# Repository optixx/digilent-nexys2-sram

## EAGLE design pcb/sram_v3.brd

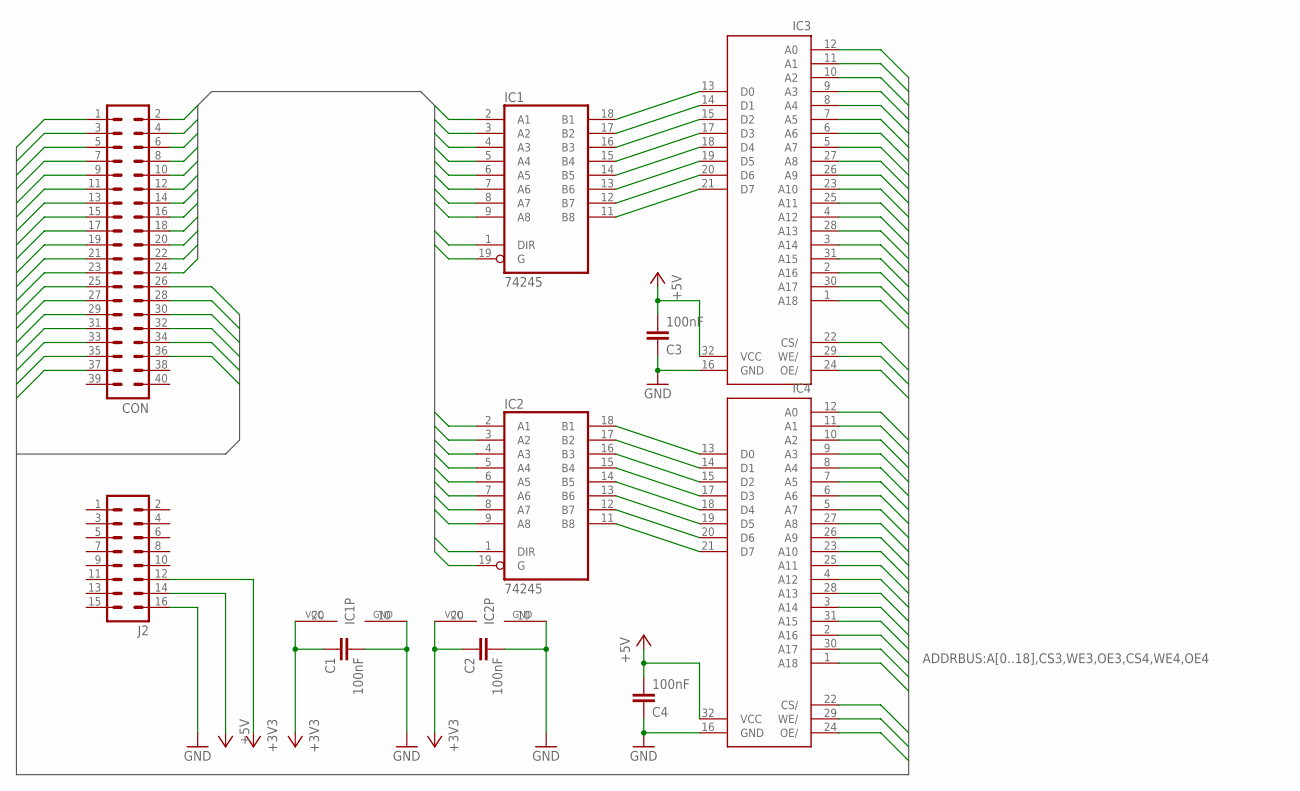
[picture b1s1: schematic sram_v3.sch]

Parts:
C1, C2, C3, C4: 100nF; C050-030X075
CON: ML40
IC1, IC2: 74245; TSSOP20
IC3, IC4: MEMORY-SAMSUNG-2_KM628512-XX; MEMORY-SAMSUNG-2_SOP-32
J2: ML16

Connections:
+3V3: C1.1, C2.1, IC1.20 (VCC), IC2.20 (VCC), J2.12
+5V: C3.2, C4.2, IC3.32 (VCC), IC4.32 (VCC), J2.14
A0: CON.37, IC3.12 (A0), IC4.12 (A0)
A1: CON.35, IC3.11 (A1), IC4.11 (A1)
A2: CON.33, IC3.10 (A2), IC4.10 (A2)
A3: CON.31, IC3.9 (A3), IC4.9 (A3)
A4: CON.29, IC3.8 (A4), IC4.8 (A4)
A5: CON.27, IC3.7 (A5), IC4.7 (A5)
A6: CON.25, IC3.6 (A6), IC4.6 (A6)
A7: CON.23, IC3.5 (A7), IC4.5 (A7)
A8: CON.21, IC3.27 (A8), IC4.27 (A8)
A9: CON.19, IC3.26 (A9), IC4.26 (A9)
A10: CON.17, IC3.23 (A10), IC4.23 (A10)
A11: CON.15, IC3.25 (A11), IC4.25 (A11)
A12: CON.13, IC3.4 (A12), IC4.4 (A12)
A13: CON.11, IC3.28 (A13), IC4.28 (A13)
A14: CON.9, IC3.3 (A14), IC4.3 (A14)
A15: CON.7, IC3.31 (A15), IC4.31 (A15)
A16: CON.5, IC3.2 (A16), IC4.2 (A16)
A17: CON.3, IC3.30 (A17), IC4.30 (A17)
A18: CON.1, IC3.1 (A18), IC4.1 (A18)
CS3: CON.26, IC3.22 (CS/)
CS4: CON.32, IC4.22 (CS/)
D0: CON.16, IC1.2 (A1), IC2.2 (A1)
D1: CON.14, IC1.3 (A2), IC2.3 (A2)
D2: CON.12, IC1.4 (A3), IC2.4 (A3)
D3: CON.10, IC1.5 (A4), IC2.5 (A4)
D4: CON.8, IC1.6 (A5), IC2.6 (A5)
D5: CON.6, IC1.7 (A6), IC2.7 (A6)
D6: CON.4, IC1.8 (A7), IC2.8 (A7)
D7: CON.2, IC1.9 (A8), IC2.9 (A8)
DIR1: CON.18, IC1.1 (DIR)
DIR2: CON.22, IC2.1 (DIR)
G1: CON.20, IC1.19 (G)
G2: CON.24, IC2.19 (G)
GND: C1.2, C2.2, C3.1, C4.1, IC1.10 (GND), IC2.10 (GND), IC3.16 (GND), IC4.16 (GND), J2.16
unnamed: IC1.18 (B1), IC3.13 (D0)
unnamed: IC1.17 (B2), IC3.14 (D1)
unnamed: IC1.16 (B3), IC3.15 (D2)
unnamed: IC1.15 (B4), IC3.17 (D3)
unnamed: IC1.14 (B5), IC3.18 (D4)
unnamed: IC1.13 (B6), IC3.19 (D5)
unnamed: IC1.12 (B7), IC3.20 (D6)
unnamed: IC1.11 (B8), IC3.21 (D7)
unnamed: IC2.18 (B1), IC4.13 (D0)
unnamed: IC2.17 (B2), IC4.14 (D1)
unnamed: IC2.16 (B3), IC4.15 (D2)
unnamed: IC2.15 (B4), IC4.17 (D3)
unnamed: IC2.14 (B5), IC4.18 (D4)
unnamed: IC2.13 (B6), IC4.19 (D5)
unnamed: IC2.12 (B7), IC4.20 (D6)
unnamed: IC2.11 (B8), IC4.21 (D7)
OE3: CON.30, IC3.24 (OE/)
OE4: CON.36, IC4.24 (OE/)
WE3: CON.28, IC3.29 (WE/)
WE4: CON.34, IC4.29 (WE/)

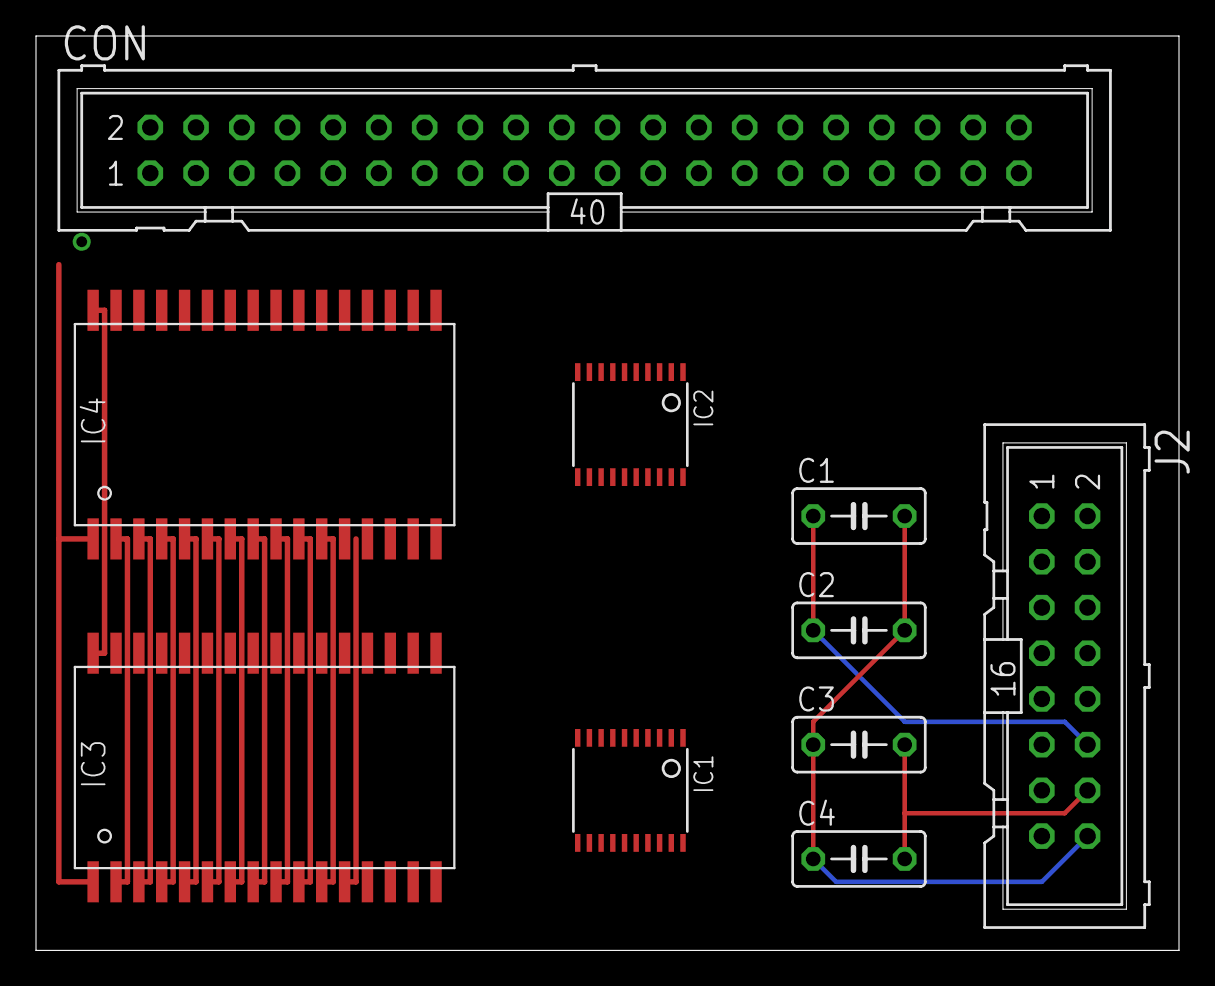
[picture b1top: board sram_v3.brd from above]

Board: 2 copper layers, 63.5 x 50.8 mm, 10 parts (0 on the bottom side), 56 nets.

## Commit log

2014-01-10 Import
2014-01-10 Add fsm
2014-01-11 Make testbench work
2014-01-15 Tweak sim
2014-01-15 Switch to 8bit databus and 19bit address bus
2014-01-16 tweak tb
2014-01-23 Add second bus driver
2014-01-23 Add docs
2014-01-23 Cleanup makefile
2014-01-26 Add schematic and board to repos
